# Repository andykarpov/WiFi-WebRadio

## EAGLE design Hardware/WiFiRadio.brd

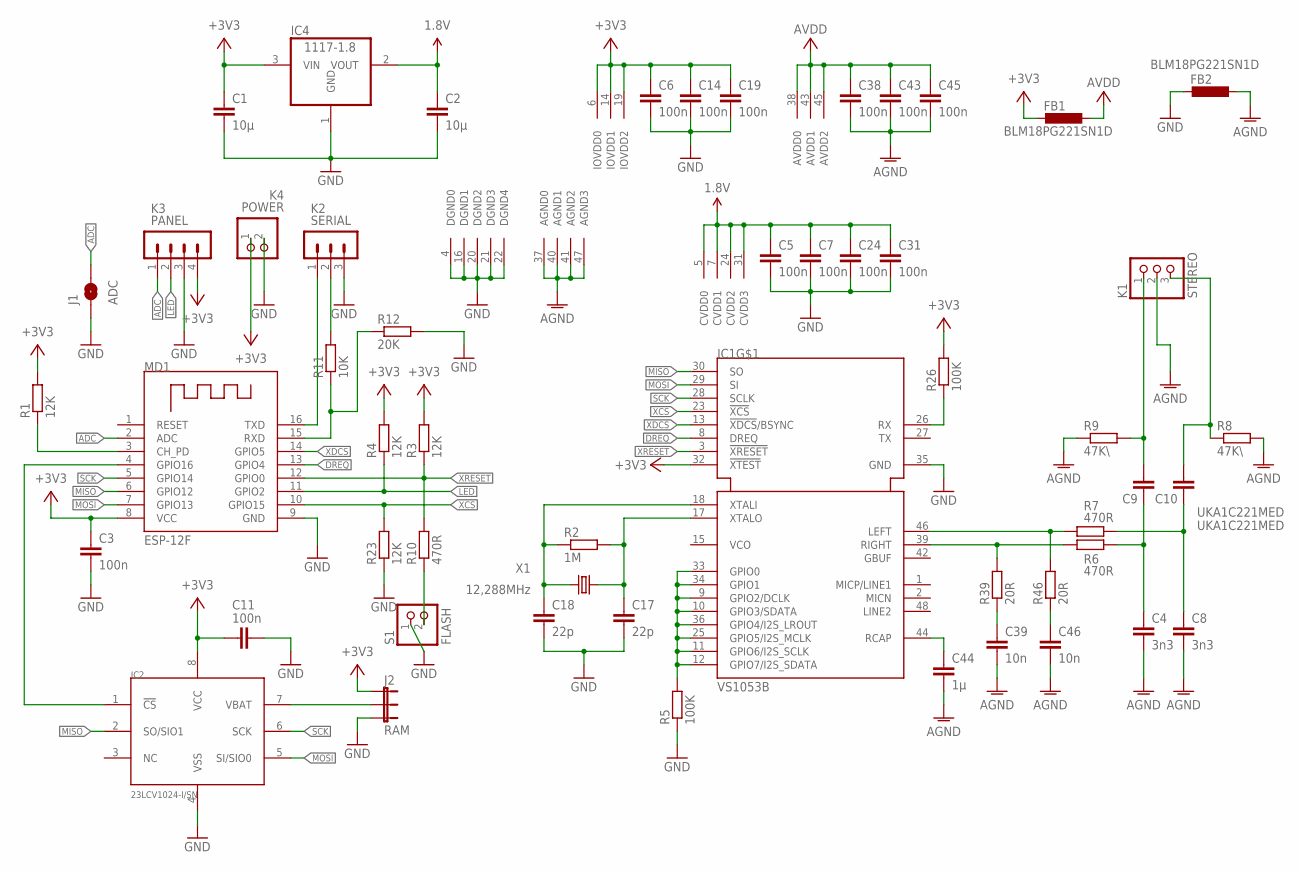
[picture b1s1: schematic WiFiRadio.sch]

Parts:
C1, C2: 10μ; C0805
C3, C5, C6, C7, C11, C14, C19, C24, C31, C38, C43, C45: 100n; C0603
C4, C8: 3n3; C0805
C9, C10: UKA1C221MED; C0805
C17, C18: 22p; C0805
C39, C46: 10n; C0805
C44: 1μ; C0805
FB1, FB2: BLM18PG221SN1D; L2012C
IC1: VS1053B; LQFP48
IC2: 23LCV1024-I/SN; SO-08
IC4: 1117-1.8; SOT223
J1: ADC; SJ_2S
J2: RAM; SJ_3
K1: STEREO; 1X03
K2: SERIAL; MA03-1
K3: PANEL; MA04-1
K4: POWER; 1X02
MD1: ESP-12F
R1, R3, R4, R23: 12K; R0805
R2: 1M; R0805
R5, R26: 100K; R0805
R6, R7, R10: 470R; R0805
R8, R9: 47K\; R0805
R11: 10K; R0603
R12: 20K; R0603
R39, R46: 20R; R0805
S1: FLASH; 1X02
X1: 12,288MHz; HC49/S

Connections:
1.8V: C2.1, C5.1, C7.1, C24.1, C31.1, IC1.5 (CVDD0), IC1.7 (CVDD1), IC1.24 (CVDD2), IC1.31 (CVDD3), IC4.2 (VOUT)
+3V3: C1.1, C3.1, C6.1, C11.1, C14.1, C19.1, FB1.2, IC1.6 (IOVDD0), IC1.14 (IOVDD1), IC1.19 (IOVDD2), IC1.32 (!XTEST), IC2.8 (VCC), IC4.3 (VIN), J2.1, K3.4, K4.1, MD1.8 (VCC), R1.2, R3.2, R4.2, R26.2
ADC: J1.2, K3.1, MD1.2 (ADC)
AGND: C4.2, C8.2, C38.2, C39.2, C43.2, C44.2, C45.2, C46.2, FB2.1, IC1.37 (AGND0), IC1.40 (AGND1), IC1.41 (AGND2), IC1.47 (AGND3), K1.2, R8.2, R9.1
DREQ: IC1.8 (DREQ), MD1.13 (GPIO4)
GND: C1.2, C2.2, C3.2, C5.2, C6.2, C7.2, C11.2, C14.2, C17.2, C18.2, C19.2, C24.2, C31.2, FB2.2, IC1.4 (DGND0), IC1.16 (DGND1), IC1.20 (DGND2), IC1.21 (DGND3), IC1.22 (DGND4), IC1.35 (GND), IC2.4 (VSS), IC4.1 (GND), J1.1, J2.3, K2.3, K3.3, K4.2, MD1.9 (GND), R5.1, R12.2, R23.1, S1.1
GPIO: IC1.9 (GPIO2/DCLK), IC1.10 (GPIO3/SDATA), IC1.11 (GPIO6/I2S_SCLK), IC1.12 (GPIO7/I2S_SDATA), IC1.25 (GPIO5/I2S_MCLK), IC1.33 (GPIO0), IC1.34 (GPIO1), IC1.36 (GPIO4/I2S_LROUT), R5.2
LED: K3.2, MD1.11 (GPIO2), R4.1
LEFT: IC1.46 (LEFT), R7.1, R46.2
MISO: IC1.30 (SO), IC2.2 (SO/SIO1), MD1.6 (GPIO12)
MOSI: IC1.29 (SI), IC2.5 (SI/SIO0), MD1.7 (GPIO13)
unnamed: IC2.1 (!CS), MD1.4 (GPIO16)
unnamed: MD1.3 (CH_PD), R1.1
unnamed: C17.1, IC1.17 (XTALO), R2.2, X1.1
unnamed: C18.1, IC1.18 (XTALI), R2.1, X1.2
unnamed: K2.2, R11.2
unnamed: C4.1, C9.1, R6.2
unnamed: C8.1, C10.1, R7.2
unnamed: IC2.7 (VBAT), J2.2
unnamed: C39.1, R39.1
unnamed: C46.1, R46.1
unnamed: C9.2, K1.1, R9.2
unnamed: C10.2, K1.3, R8.1
unnamed: R10.1, S1.2
RCAP: C44.1, IC1.44 (RCAP)
RIGHT: IC1.39 (RIGHT), R6.1, R39.2
RX: IC1.26 (RX), R26.1
RXD: MD1.15 (RXD), R11.1, R12.1
SCK: IC1.28 (SCLK), IC2.6 (SCK), MD1.5 (GPIO14)
TXD: K2.1, MD1.16 (TXD)
V+: C38.1, C43.1, C45.1, FB1.1, IC1.38 (AVDD0), IC1.43 (AVDD1), IC1.45 (AVDD2)
XCS: IC1.23 (!XCS), MD1.10 (GPIO15), R23.2
XDCS: IC1.13 (!XDCS!/BSYNC), MD1.14 (GPIO5)
XRESET: IC1.3 (!XRESET), MD1.12 (GPIO0), R3.1, R10.2

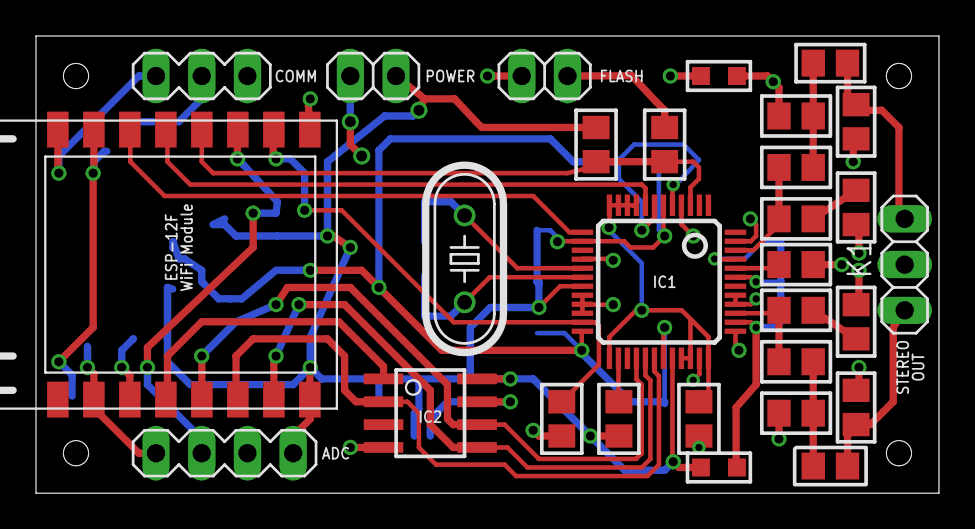
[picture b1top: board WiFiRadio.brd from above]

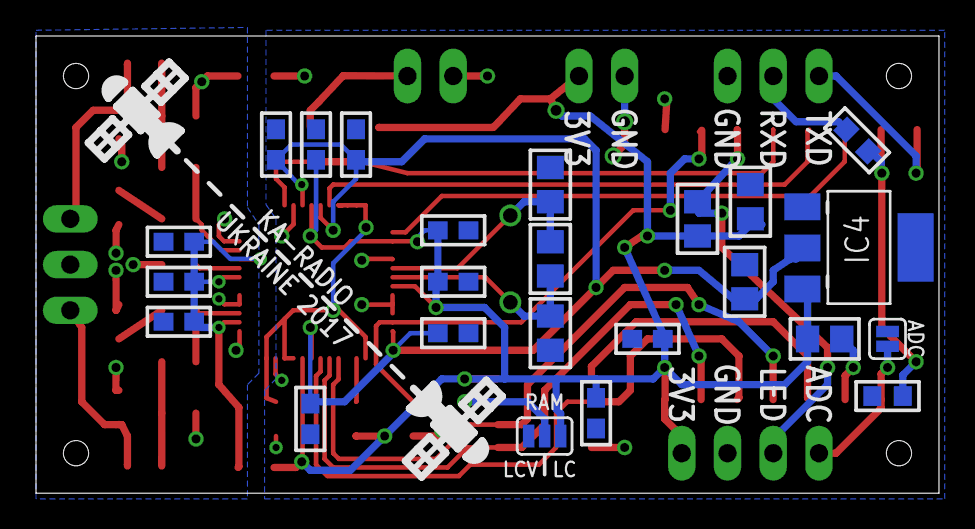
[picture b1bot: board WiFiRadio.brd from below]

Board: 2 copper layers, 50.2 x 25.4 mm, 53 parts (24 on the bottom side), 34 nets.

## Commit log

2017-04-07 new (smaller) pcb for personal needs, removed 5v and 3v3 regulators, added other small improvements

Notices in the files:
parts and their libraries:
SparkFun-Retired: Licensing:Creative Commons ShareAlike 4.0 International - https://creativecommons.org/licenses/by-sa/4.0
